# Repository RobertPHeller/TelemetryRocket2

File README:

This is a design for a 2-stage model rocket that will boost a basic 
ESP32-based telemetry board (accelerometer, altimeter, barometric pressure 
sensor, and temperature sensor, along with a real time clock).  The telemetry 
readings are saved on a MicroSD card on the TTGO-T1 board using its MicroSD 
slot. The system is powered by a LiPo battery while in flight and the integrated
battery charger on the TTGO-T1 board is used to charge the battery via the 
micro-B USB connector.  The sketch uses the USB connection for serial communication
to set the RTC and open the log file.

The first stage has a four engine cluster, with 1 E12-0 and three D12-3 
engines.  The second stage takes one E12-8 engine.

Both stages have parachute recovery.  The first stage has three (small) parachutes 
above the outer three engines.  The upper stage has a single (large) parachute.

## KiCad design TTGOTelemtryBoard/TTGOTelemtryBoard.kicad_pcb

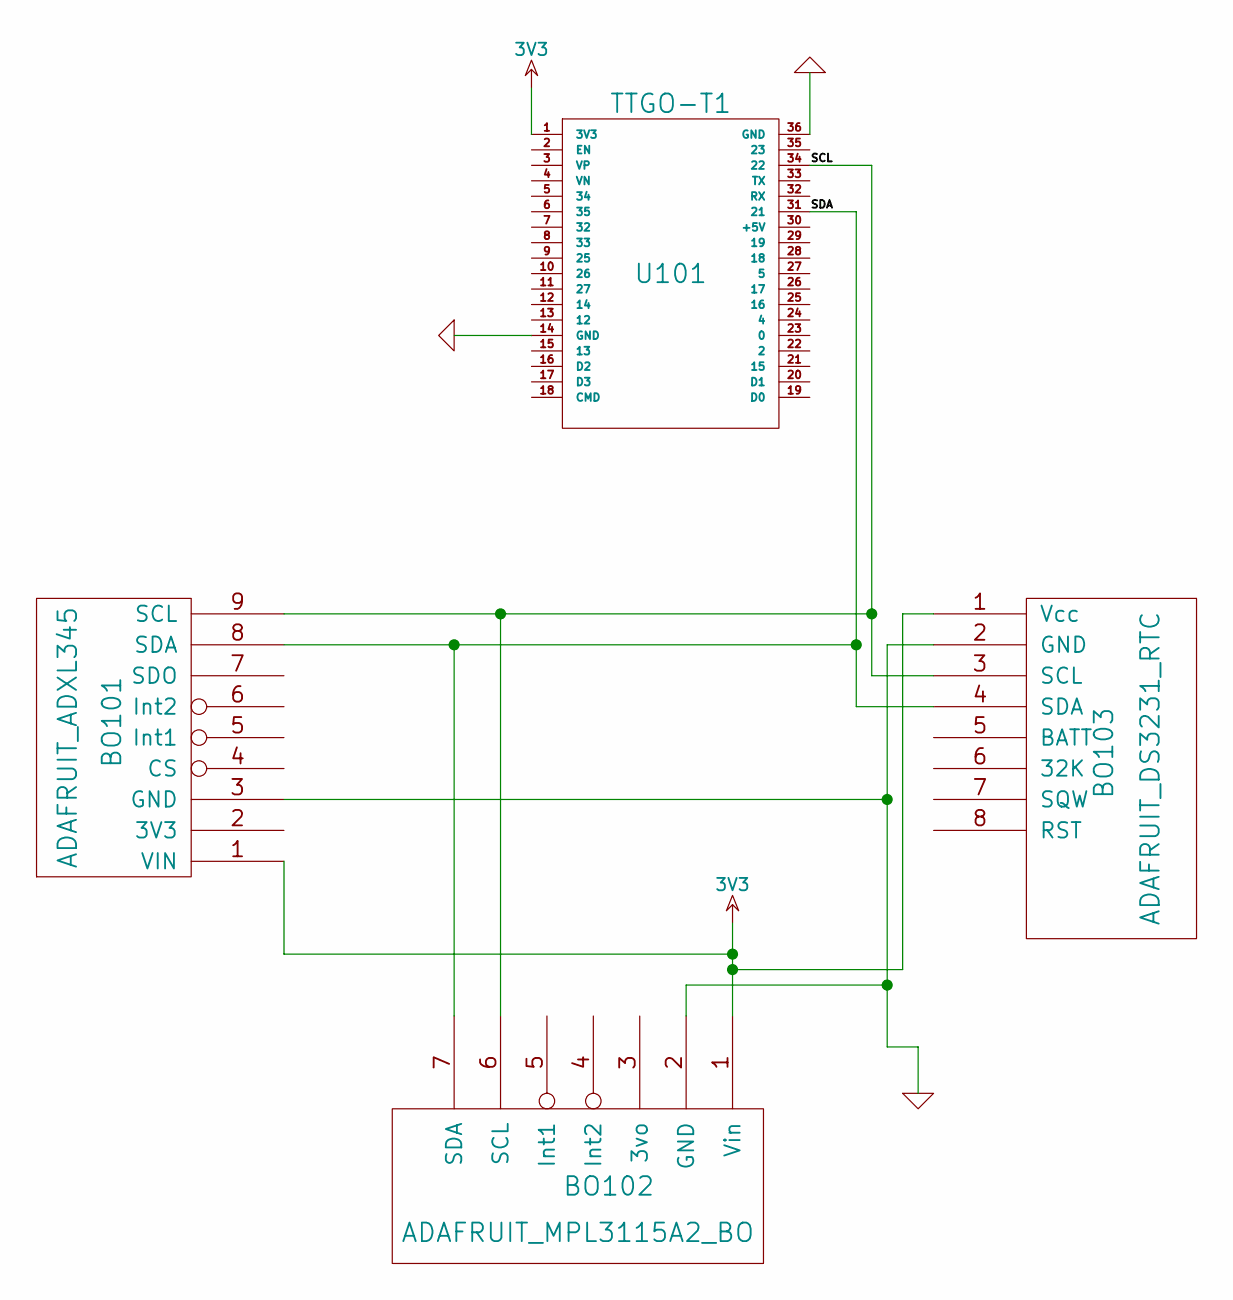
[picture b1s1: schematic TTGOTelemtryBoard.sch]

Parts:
BO101: ADAFRUIT_ADXL345
BO102: ADAFRUIT_MPL3115A2_BO
BO103: ADAFRUIT_DS3231_RTC
U101: TTGO-T1

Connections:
3V3: BO101.1 (VIN), BO102.1 (Vin), BO103.1 (Vcc), U101.1 (3V3)
/SCL: BO101.9 (SCL), BO102.6 (SCL), BO103.3 (SCL), U101.34 (22)
/SDA: BO101.8 (SDA), BO102.7 (SDA), BO103.4 (SDA), U101.31 (21)
GND: BO101.3 (GND), BO102.2 (GND), BO103.2 (GND), U101.14 (GND), U101.36 (GND)

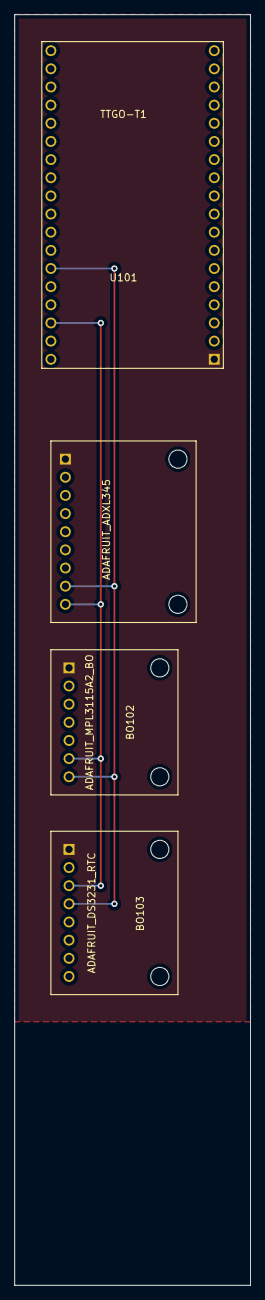
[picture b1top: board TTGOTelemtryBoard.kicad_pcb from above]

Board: 2 copper layers, 33.0 x 177.8 mm, 4 parts (0 on the bottom side), 4 nets.

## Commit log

2020-08-20 Updated sources
2020-08-20 Fix small typo.
2020-08-20 Add KiCAD files for the PCB.
2020-08-21 Add Rocket Front Image.
2020-08-21 Add rotated, cropped, and scaled image.
